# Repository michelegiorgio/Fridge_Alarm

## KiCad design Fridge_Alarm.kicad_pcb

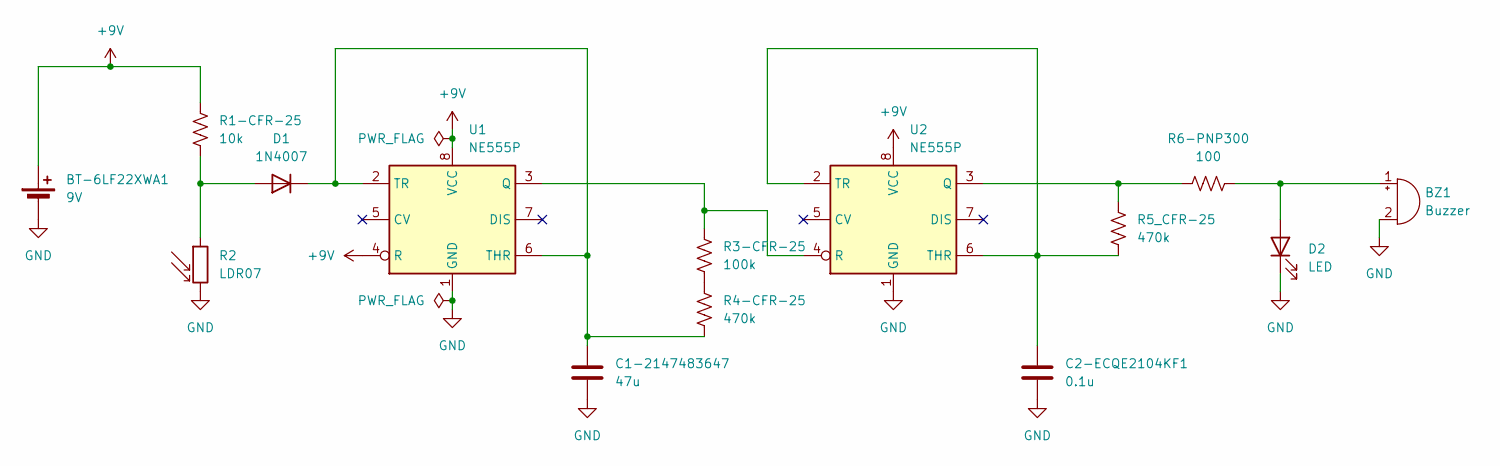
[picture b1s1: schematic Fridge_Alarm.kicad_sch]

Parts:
BT-6LF22XWA1: 9V; Pins_Battery
BZ1: Buzzer; C_Radial_D12.5mm_H20.0mm_P5.00mm
C1-2147483647: 47u; CP_Radial_D5.0mm_P2.00mm
C2-ECQE2104KF1: 0.1u; C_Disc_D10.5mm_W5.0mm_P7.50mm
D1: 1N4007; D_DO-41_SOD81_P10.16mm_Horizontal
D2: LED; LED_D4.0mm
R1-CFR-25: 10k; R_Axial_DIN0207_L6.3mm_D2.5mm_P10.16mm_Horizontal
R2: LDR07; R_LDR_5.1x4.3mm_P3.4mm_Vertical
R3-CFR-25: 100k; R_Axial_DIN0207_L6.3mm_D2.5mm_P10.16mm_Horizontal
R4-CFR-25, R5_CFR-25: 470k; R_Axial_DIN0207_L6.3mm_D2.5mm_P10.16mm_Horizontal
R6-PNP300: 100; R_Axial_DIN0414_L11.9mm_D4.5mm_P20.32mm_Horizontal
U1, U2: NE555P; DIP-8_W7.62mm

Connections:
+9V: BT-6LF22XWA1.1 (+), R1-CFR-25.1, U1.4 (R), U1.8 (VCC), U2.8 (VCC)
GND: BT-6LF22XWA1.2 (-), BZ1.2 (-), C1-2147483647.2, C2-ECQE2104KF1.2, D2.1 (K), R2.2, U1.1 (GND), U2.1 (GND)
unnamed: BZ1.1 (+), D2.2 (A), R6-PNP300.2
unnamed: D1.2 (A), R1-CFR-25.2, R2.1
unnamed: C1-2147483647.1, D1.1 (K), R4-CFR-25.2, U1.2 (TR), U1.6 (THR)
unnamed: R3-CFR-25.2, R4-CFR-25.1
unnamed: R3-CFR-25.1, U1.3 (Q), U2.4 (R)
unnamed: R5_CFR-25.1, R6-PNP300.1, U2.3 (Q)
unnamed: C2-ECQE2104KF1.1, R5_CFR-25.2, U2.2 (TR), U2.6 (THR)

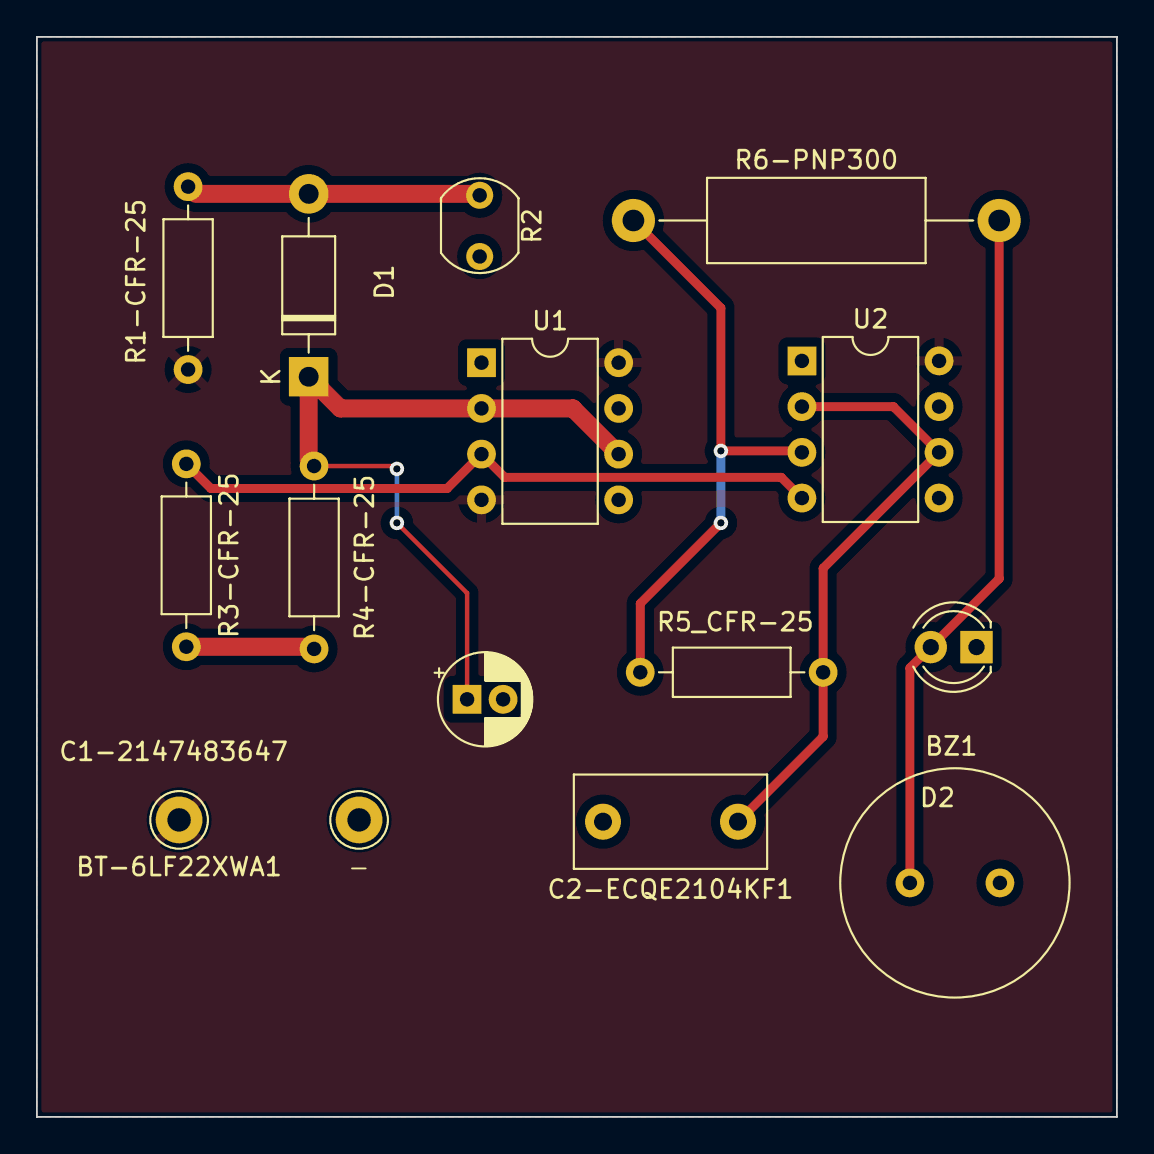
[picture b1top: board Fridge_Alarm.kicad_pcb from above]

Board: 2 copper layers, 60.0 x 60.0 mm, 14 parts (0 on the bottom side), 9 nets.

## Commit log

2024-04-03 Kicad Project Files
